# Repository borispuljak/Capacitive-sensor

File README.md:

Capacitive distance sensors are increasingly used with the advancement of technology due to their many advantages such as low power consumption, precision, speed, etc. They work on the principle of observing the change in capacitance between the sensor and the object when the object approaches or moves away from it. In the practical part of the work, a prototype of a directional capacitive sensor was created and controlled by an Arduino Uno microcontroller. Measurements related to the functionality of the assembly were carried out, observing the voltage values and forms depending on the position of the object in relation to the sensor. Based on the measurement results, it was concluded that the ideal distance between the sensor and reference plate is 1 cm and that then the sensor reads the object at a distance of 30 cm or closer.

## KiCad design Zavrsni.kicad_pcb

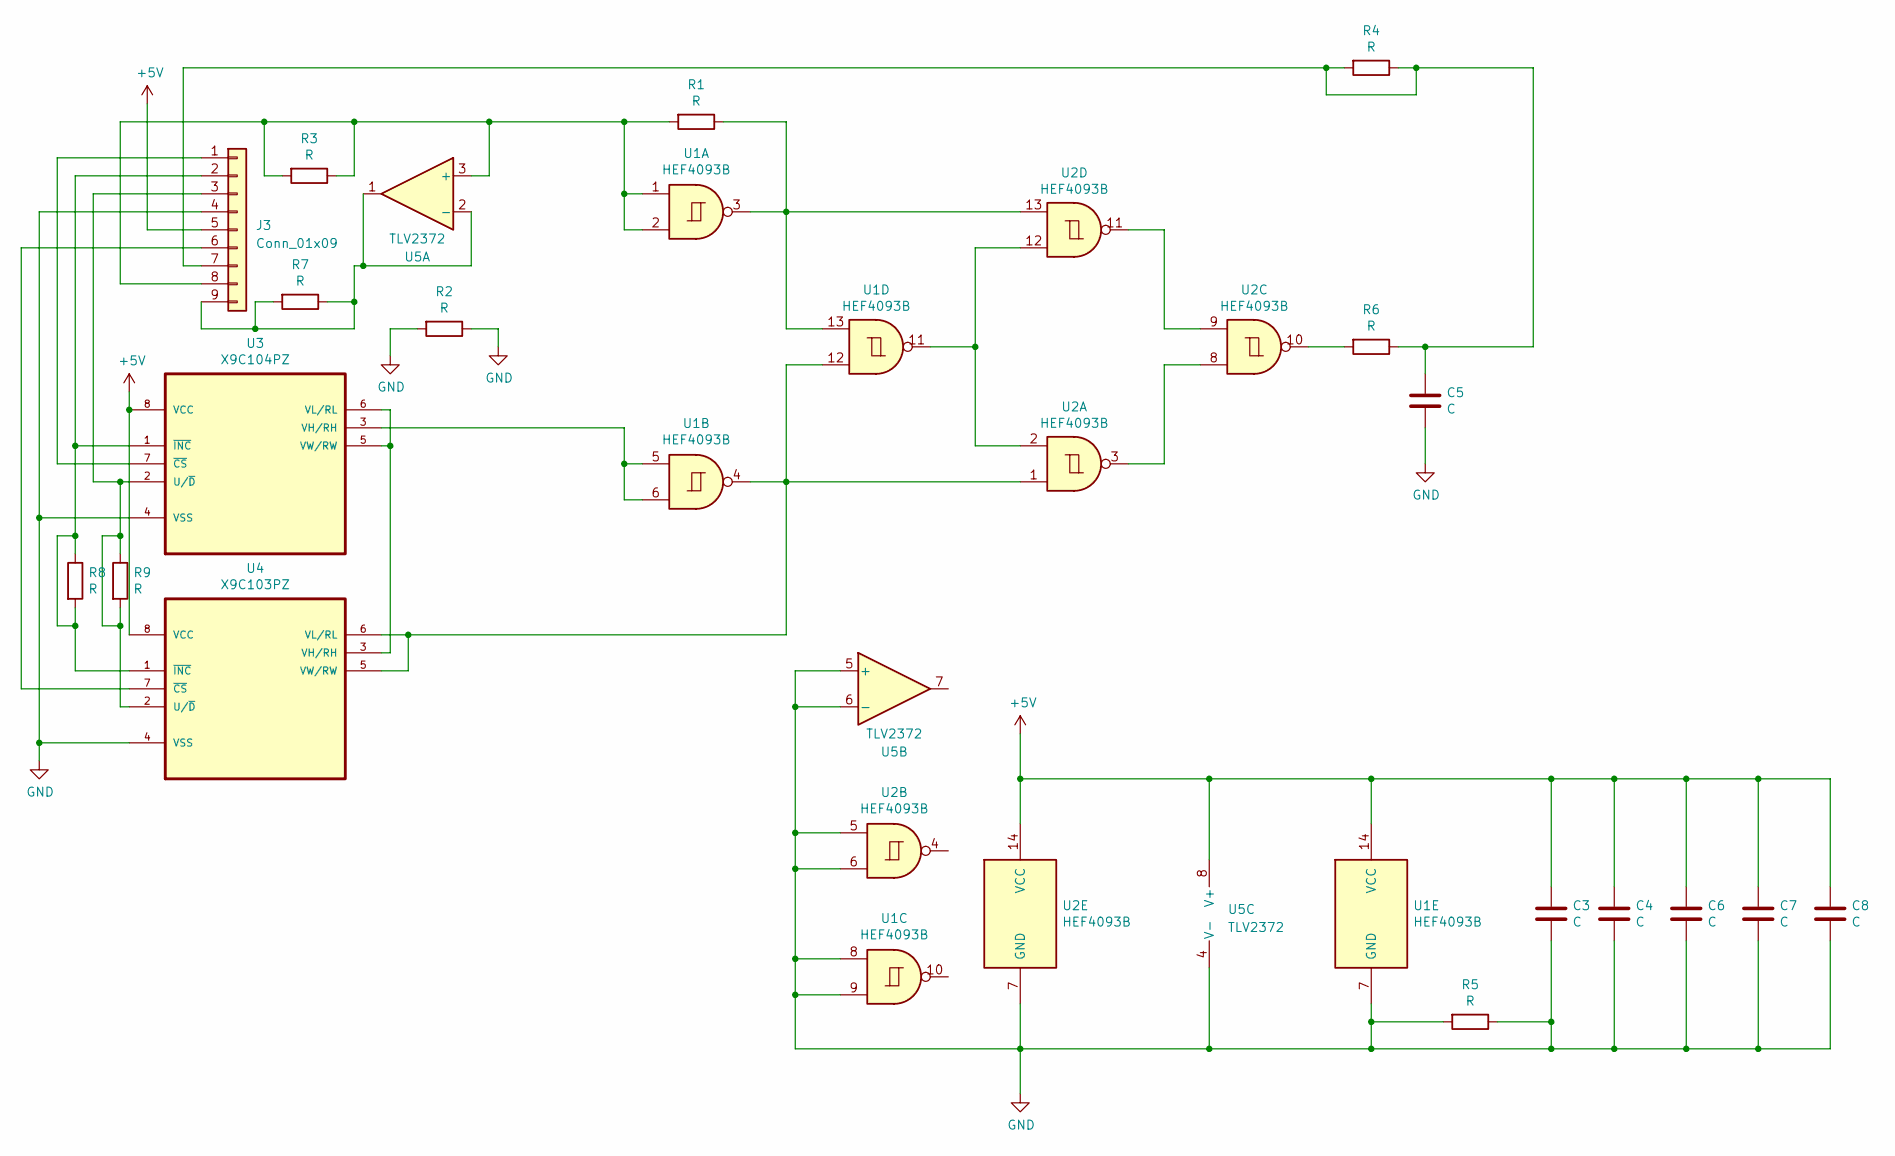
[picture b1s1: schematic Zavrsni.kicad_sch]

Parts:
C3, C4, C5, C6, C7, C8: C; C_Disc_D3.0mm_W1.6mm_P2.50mm
J3: Conn_01x09; PinHeader_1x09_P2.54mm_Horizontal
R1, R4, R5, R6, R8, R9: R; R_Axial_DIN0204_L3.6mm_D1.6mm_P7.62mm_Horizontal
R2, R3, R7: R; R_Axial_DIN0204_L3.6mm_D1.6mm_P5.08mm_Horizontal
U1, U2: HEF4093B; DIP-14_W7.62mm
U3: X9C104PZ; DIP-8_W7.62mm; MPN X9C102PZ
U4: X9C103PZ; DIP-8_W7.62mm; MPN X9C102PZ
U5: TLV2372; DIP-8_W7.62mm

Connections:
+5V: C3.1, C4.1, C6.1, C7.1, C8.1, J3.5, U1.14 (VCC), U2.14 (VCC), U3.8 (VCC), U4.8 (VCC), U5.8 (V+)
GND: C3.2, C4.2, C5.2, C6.2, C7.2, C8.2, J3.4, R2.1, R2.2, R5.1, R5.2, U1.7 (GND), U1.8, U1.9, U2.5, U2.6, U2.7 (GND), U3.4 (VSS), U4.4 (VSS), U5.4 (V-), U5.5 (+), U5.6 (-)
unnamed: J3.1, U3.7 (~CS)
unnamed: J3.2, R8.1, R8.2, U3.1 (~INC), U4.1 (~INC)
unnamed: J3.3, R9.1, R9.2, U3.2 (U/~D), U4.2 (U/~D)
unnamed: J3.6, U4.7 (~CS)
unnamed: C5.1, J3.7, R4.1, R4.2, R6.1
unnamed: J3.8, R1.2, R3.1, R3.2, U1.1, U1.2, U5.3 (+)
unnamed: J3.9, R7.1, R7.2, U5.1, U5.2 (-)
unnamed: R1.1, U1.3, U1.13, U2.13
unnamed: R6.2, U2.10
unnamed: U1.11, U2.2, U2.12
unnamed: U2.3, U2.8
unnamed: U2.9, U2.11
unnamed: U1.5, U1.6, U3.3 (VH/RH)
unnamed: U3.5 (VW/RW), U3.6 (VL/RL), U4.3 (VH/RH)
unnamed: U1.4, U1.12, U2.1, U4.5 (VW/RW), U4.6 (VL/RL)

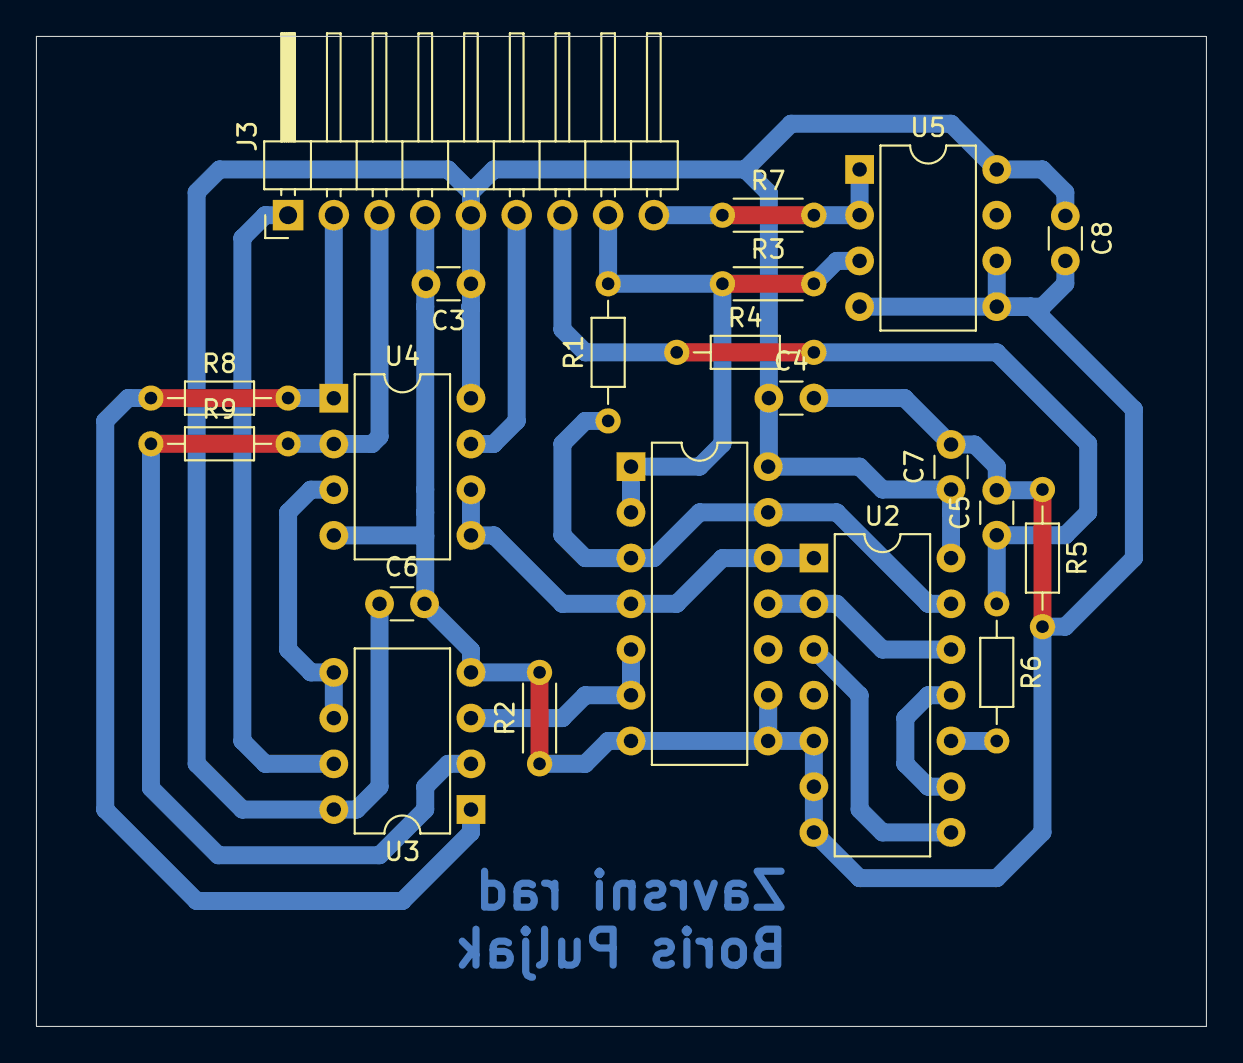
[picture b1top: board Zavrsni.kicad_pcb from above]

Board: 2 copper layers, 65.0 x 55.0 mm, 21 parts (0 on the bottom side), 17 nets.

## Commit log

2023-07-06 Kicad dio
